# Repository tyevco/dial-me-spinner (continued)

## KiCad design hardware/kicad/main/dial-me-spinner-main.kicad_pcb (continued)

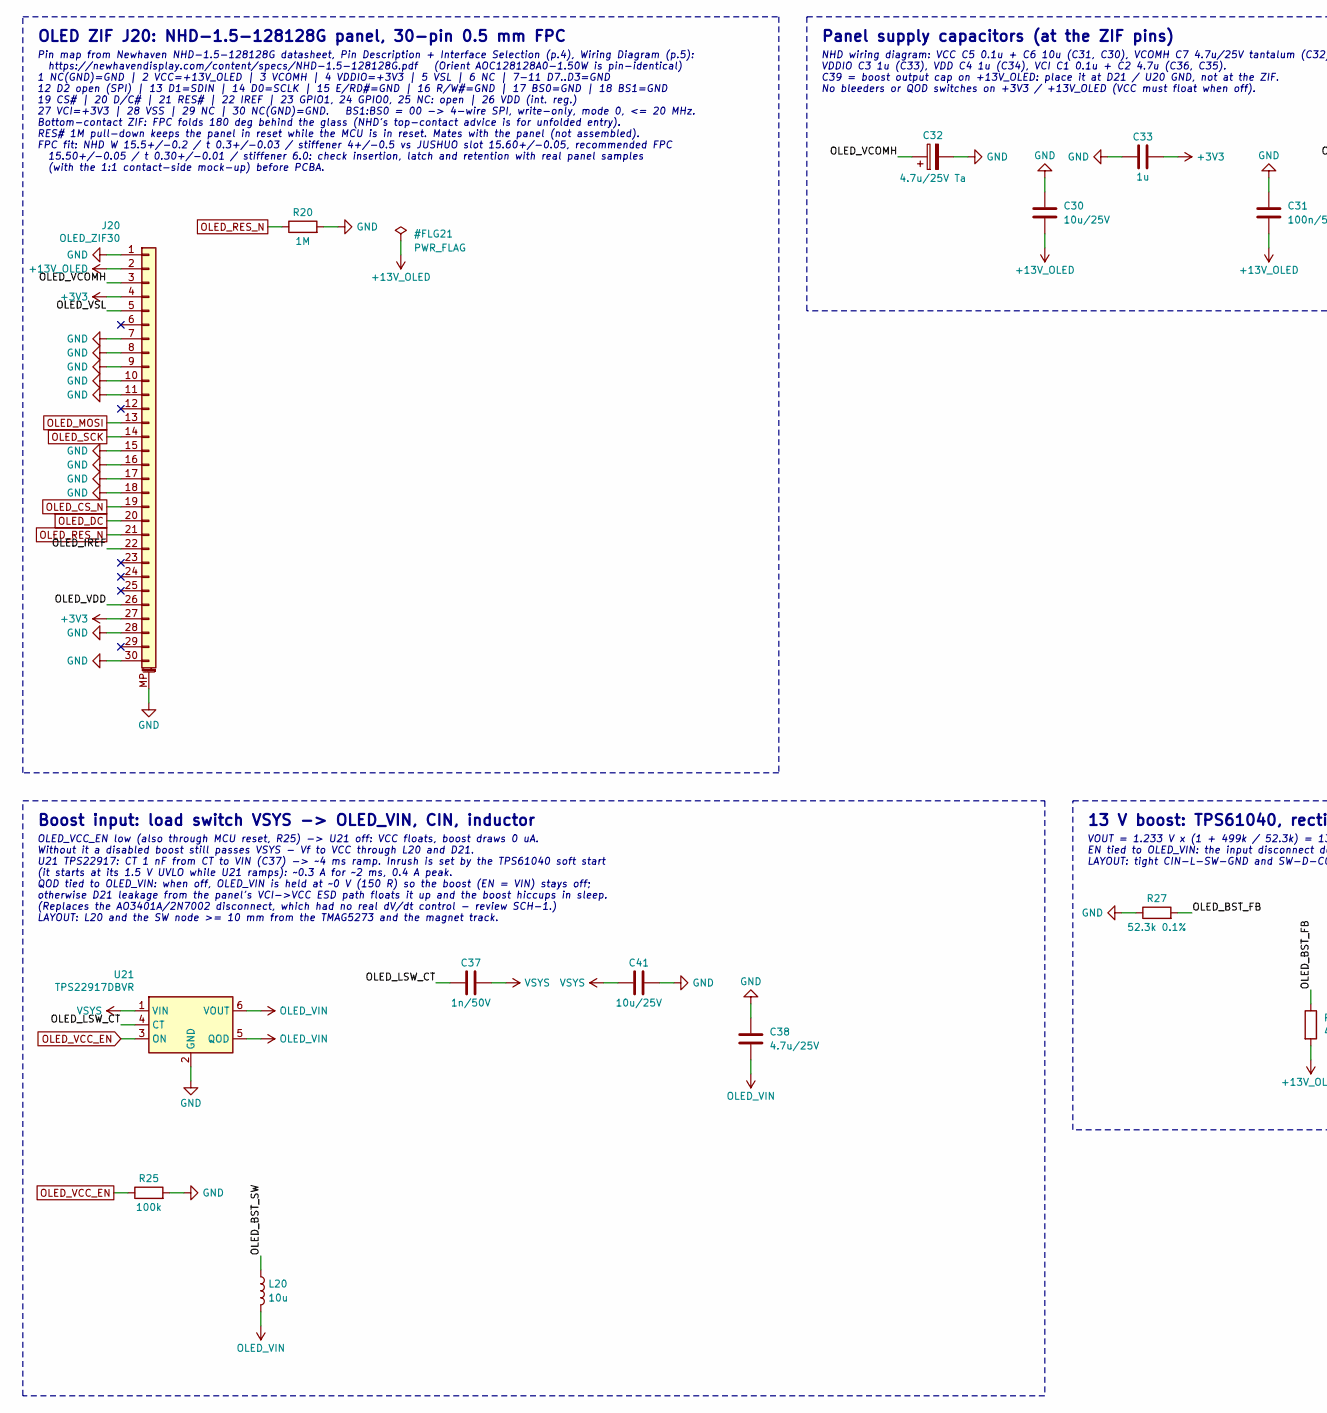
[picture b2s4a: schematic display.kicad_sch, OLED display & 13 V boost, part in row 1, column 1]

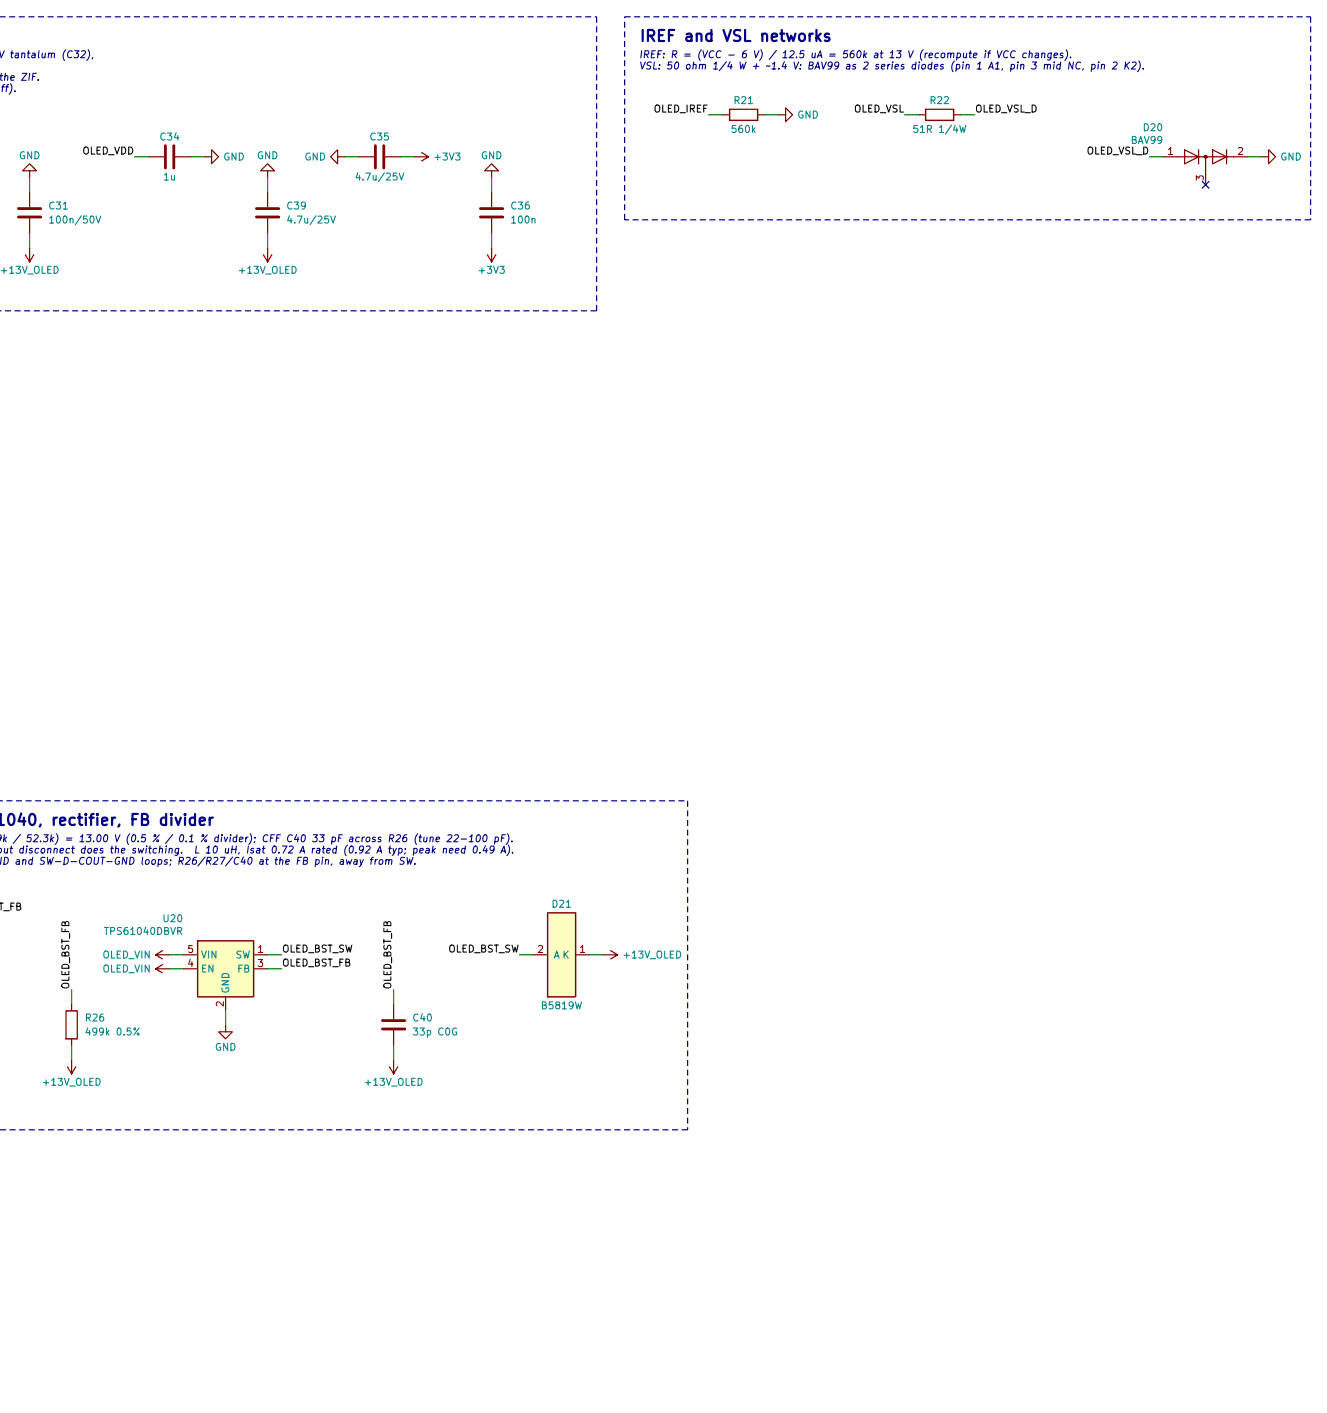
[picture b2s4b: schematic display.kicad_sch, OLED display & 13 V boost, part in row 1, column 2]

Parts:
C30: 10u/25V; C_0805_2012Metric; MPN CL21A106KAYNNNE; LCSC C15850
C31: 100n/50V; C_0402_1005Metric; MPN CL05B104KB54PNC; LCSC C307331
C32: 4.7u/25V Ta; CP_EIA-3216-18_Kemet-A; MPN TAJA475K025RNJ; LCSC C7189
C33, C34: 1u; C_0402_1005Metric; MPN CL05A105KA5NQNC; LCSC C52923
C35, C38, C39: 4.7u/25V; C_0805_2012Metric; MPN CL21A475KAQNNNE; LCSC C1779
C36: 100n; C_0402_1005Metric; MPN CL05B104KO5NNNC; LCSC C1525
C37: 1n/50V; C_0402_1005Metric; MPN 0402B102K500NT; LCSC C1523
C40: 33p C0G; C_0402_1005Metric; MPN 0402CG330J500NT; LCSC C1562
C41: 10u/25V; C_0603_1608Metric; MPN CL10A106MA8NRNC; LCSC C96446
D20: BAV99; SOT-23; MPN BAV99,215; LCSC C2500
D21: B5819W; D_SOD-123; MPN B5819W SL; LCSC C8598
J20: OLED_ZIF30; JUSHUO_AFC01-S30FCA-00_1x30-1MP_P0.50mm_Horizontal; MPN AFC01-S30FCA-00; LCSC C262671
L20: 10u; L_Sunlord_SWPA3015S; MPN SWPA3015S100MT; LCSC C45403
R20: 1M; R_0402_1005Metric; MPN 0402WGF1004TCE; LCSC C26083
R21: 560k; R_0402_1005Metric; MPN 0402WGF5603TCE; LCSC C132339
R22: 51R 1/4W; R_1206_3216Metric; MPN 1206W4F510JT5E; LCSC C18019
R25: 100k; R_0402_1005Metric; MPN 0402WGF1003TCE; LCSC C25741
R26: 499k 0.5%; R_0402_1005Metric; MPN RC0402DR-07499KL; LCSC C4167968
R27: 52.3k 0.1%; R_0402_1005Metric; MPN RT0402BRD0752K3L; LCSC C852832
U20: TPS61040DBVR; SOT-23-5; MPN TPS61040DBVR; LCSC C7722
U21: TPS22917DBVR; SOT-23-6; MPN TPS22917DBVR; LCSC C2681320

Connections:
+3V3: C33.2, C35.2, C36.2, J20.4, J20.27; also elsewhere on the board
+13V_OLED: C30.2, C31.2, C39.2, C40.2, D21.1 (K), J20.2, R26.2
/OLED display & 13 V boost/OLED_BST_FB: C40.1, R26.1, R27.2, U20.3 (FB)
/OLED display & 13 V boost/OLED_BST_SW: D21.2 (A), L20.1, U20.1 (SW)
/OLED display & 13 V boost/OLED_IREF: J20.22, R21.1
/OLED display & 13 V boost/OLED_LSW_CT: C37.1, U21.4 (CT)
/OLED display & 13 V boost/OLED_VCOMH: C32.1, J20.3
/OLED display & 13 V boost/OLED_VDD: C34.1, J20.26
/OLED display & 13 V boost/OLED_VSL: J20.5, R22.1
/OLED display & 13 V boost/OLED_VSL_D: D20.1 (K), R22.2
GND: C30.1, C31.1, C32.2, C33.1, C34.2, C35.1, C36.1, C38.1, C39.1, C41.2, D20.2 (A), J20.1, J20.7, J20.8, J20.9, J20.10, J20.11, J20.15, J20.16, J20.17, J20.18, J20.28, J20.30, J20.MP (MountPin), R20.2, R21.2, R25.2, R27.1, U20.2 (GND), U21.2 (GND); also elsewhere on the board
OLED_CS_N: J20.19; also elsewhere on the board
OLED_DC: J20.20; also elsewhere on the board
OLED_MOSI: J20.13; also elsewhere on the board
OLED_RES_N: J20.21, R20.1; also elsewhere on the board
OLED_SCK: J20.14; also elsewhere on the board
OLED_VCC_EN: R25.1, U21.3 (ON); also elsewhere on the board
OLED_VIN: C38.2, L20.2, U20.4 (EN), U20.5 (VIN), U21.5 (QOD), U21.6 (VOUT)
VSYS: C37.2, C41.1, U21.1 (VIN); also elsewhere on the board

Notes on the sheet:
OLED ZIF J20: NHD-1.5-128128G panel, 30-pin 0.5 mm FPC
Pin map from Newhaven NHD-1.5-128128G datasheet, Pin Description + Interface Selection (p.4), Wiring Diagram (p.5): https://newhavendisplay.com/content/specs/NHD-1.5-128128G.pdf (Orient AOC128128A0-1.50W is pin-identical) 1 NC(GND)=GND | 2 VCC=+13V_OLED | 3 VCOMH | 4 VDDIO=+3V3 | 5 VSL | 6 NC | 7-1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
Panel supply capacitors (at the ZIF pins)
NHD wiring diagram: VCC C5 0.1u + C6 10u (C31, C30), VCOMH C7 4.7u/25V tantalum (C32), VDDIO C3 1u (C33), VDD C4 1u (C34), VCI C1 0.1u + C2 4.7u (C36, C35). C39 = boost output cap on +13V_OLED: place it at D21 / U20 GND, not at the ZIF. No bleeders or QOD switches on +3V3 / +13V_OLED (VCC must floa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
IREF and VSL networks
IREF: R = (VCC - 6 V) / 12.5 uA = 560k at 13 V (recompute if VCC changes). VSL: 50 ohm 1/4 W + ~1.4 V: BAV99 as 2 series diodes (pin 1 A1, pin 3 mid NC, pin 2 K2).
Boost input: load switch VSYS -> OLED_VIN, CIN, inductor
OLED_VCC_EN low (also through MCU reset, R25) -> U21 off: VCC floats, boost draws 0 uA. Without it a disabled boost still passes VSYS - Vf to VCC through L20 and D21. U21 TPS22917: CT 1 nF from CT to VIN (C37) -> ~4 ms ramp. Inrush is set by the TPS61040 soft start (it starts at its 1.5 V UVLO whil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
13 V boost: TPS61040, rectifier, FB divider
VOUT = 1.233 V x (1 + 499k / 52.3k) = 13.00 V (0.5 % / 0.1 % divider); CFF C40 33 pF across R26 (tune 22-100 pF). EN tied to OLED_VIN: the input disconnect does the switching. L 10 uH, Isat 0.72 A rated (0.92 A typ; peak need 0.49 A). LAYOUT: tight CIN-L-SW-GND and SW-D-COUT-GND loops; R26/R27/C40 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

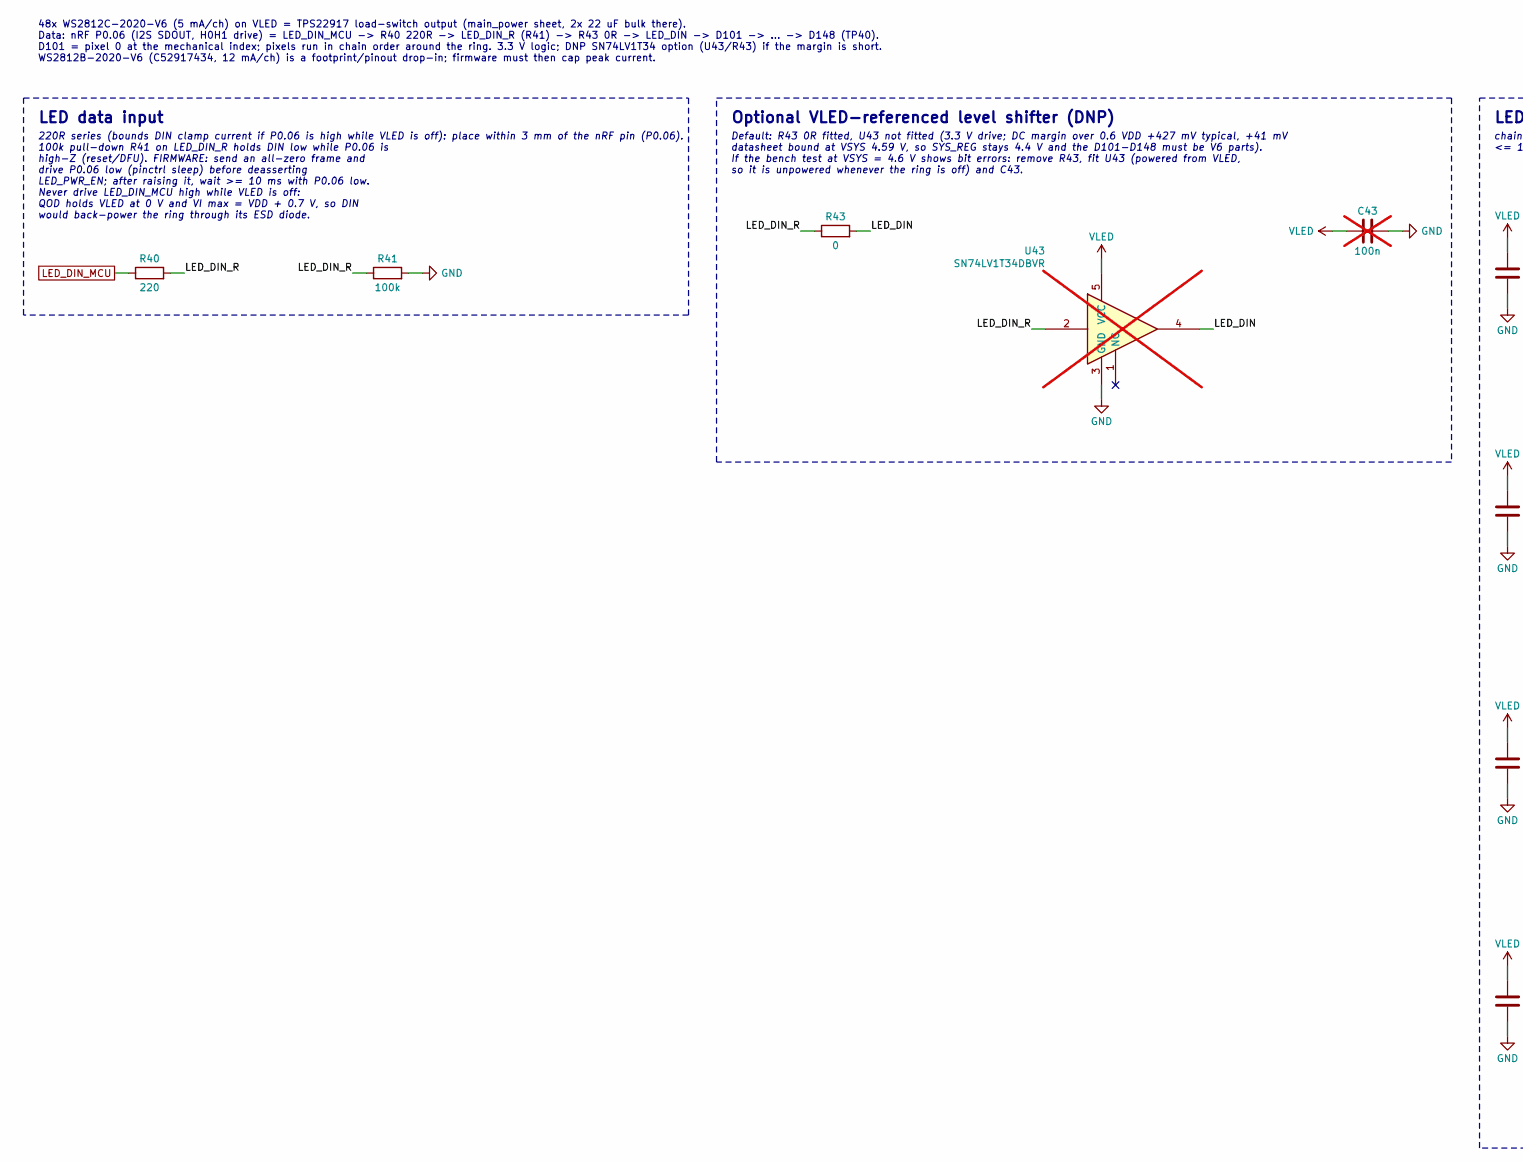
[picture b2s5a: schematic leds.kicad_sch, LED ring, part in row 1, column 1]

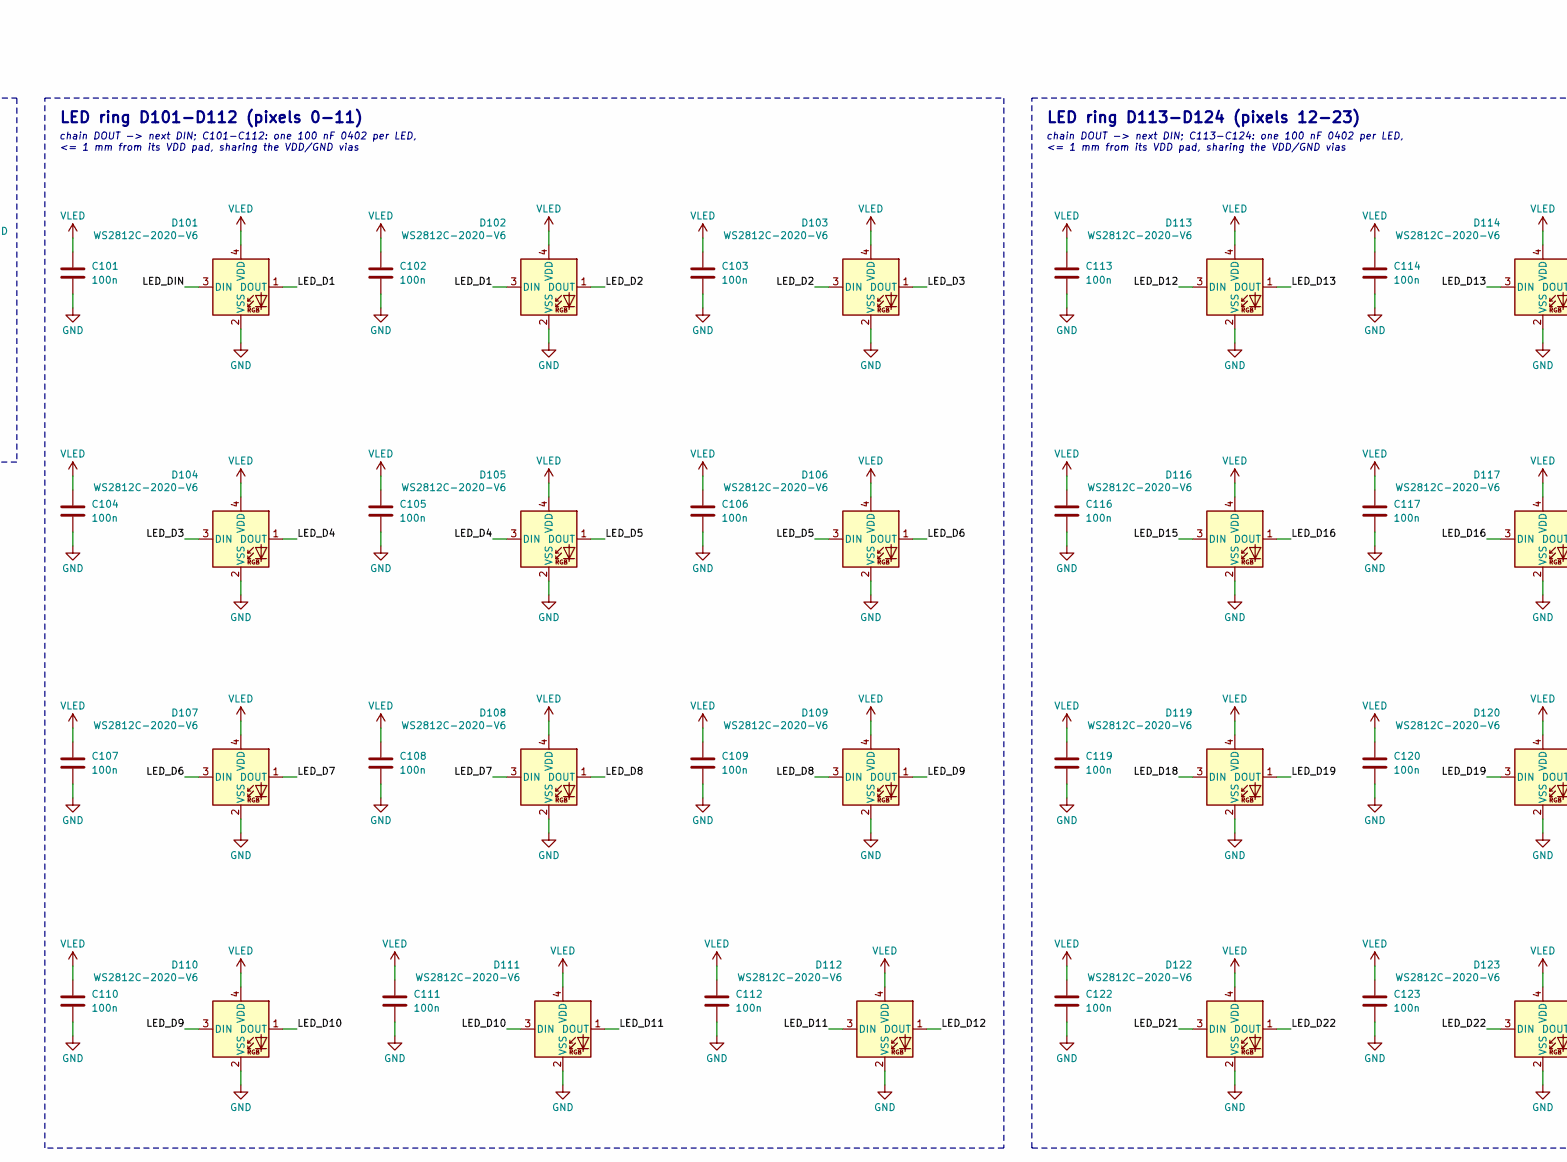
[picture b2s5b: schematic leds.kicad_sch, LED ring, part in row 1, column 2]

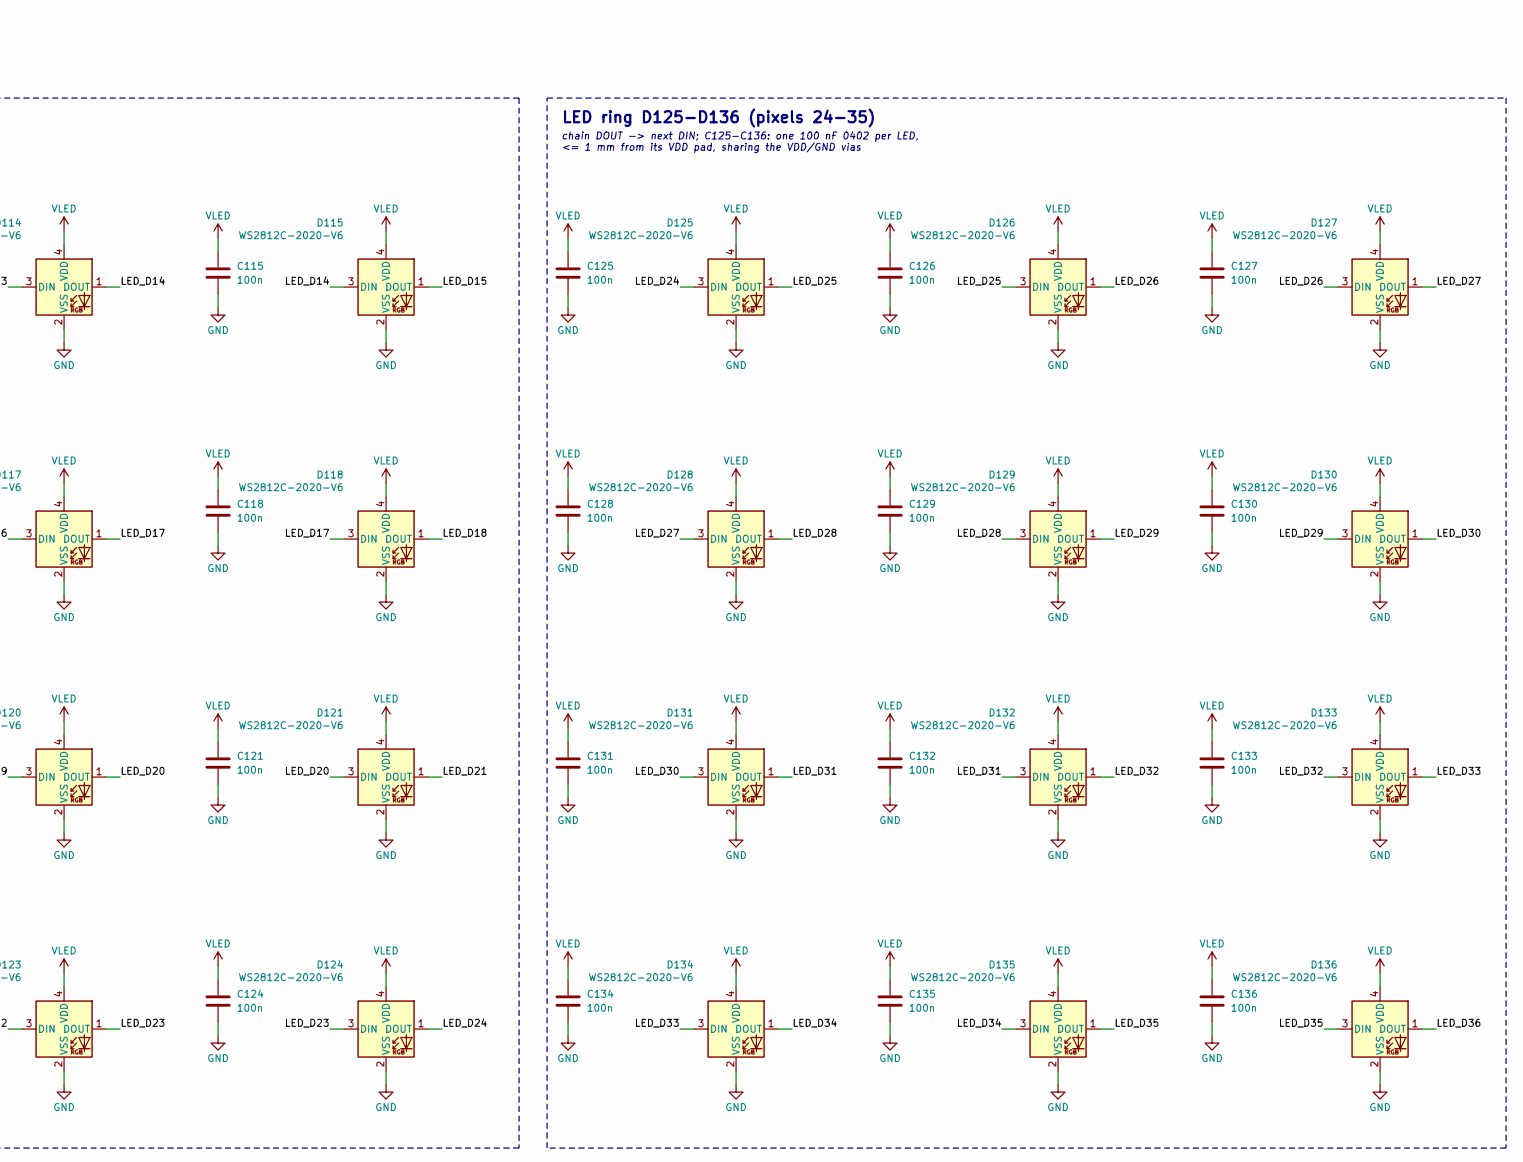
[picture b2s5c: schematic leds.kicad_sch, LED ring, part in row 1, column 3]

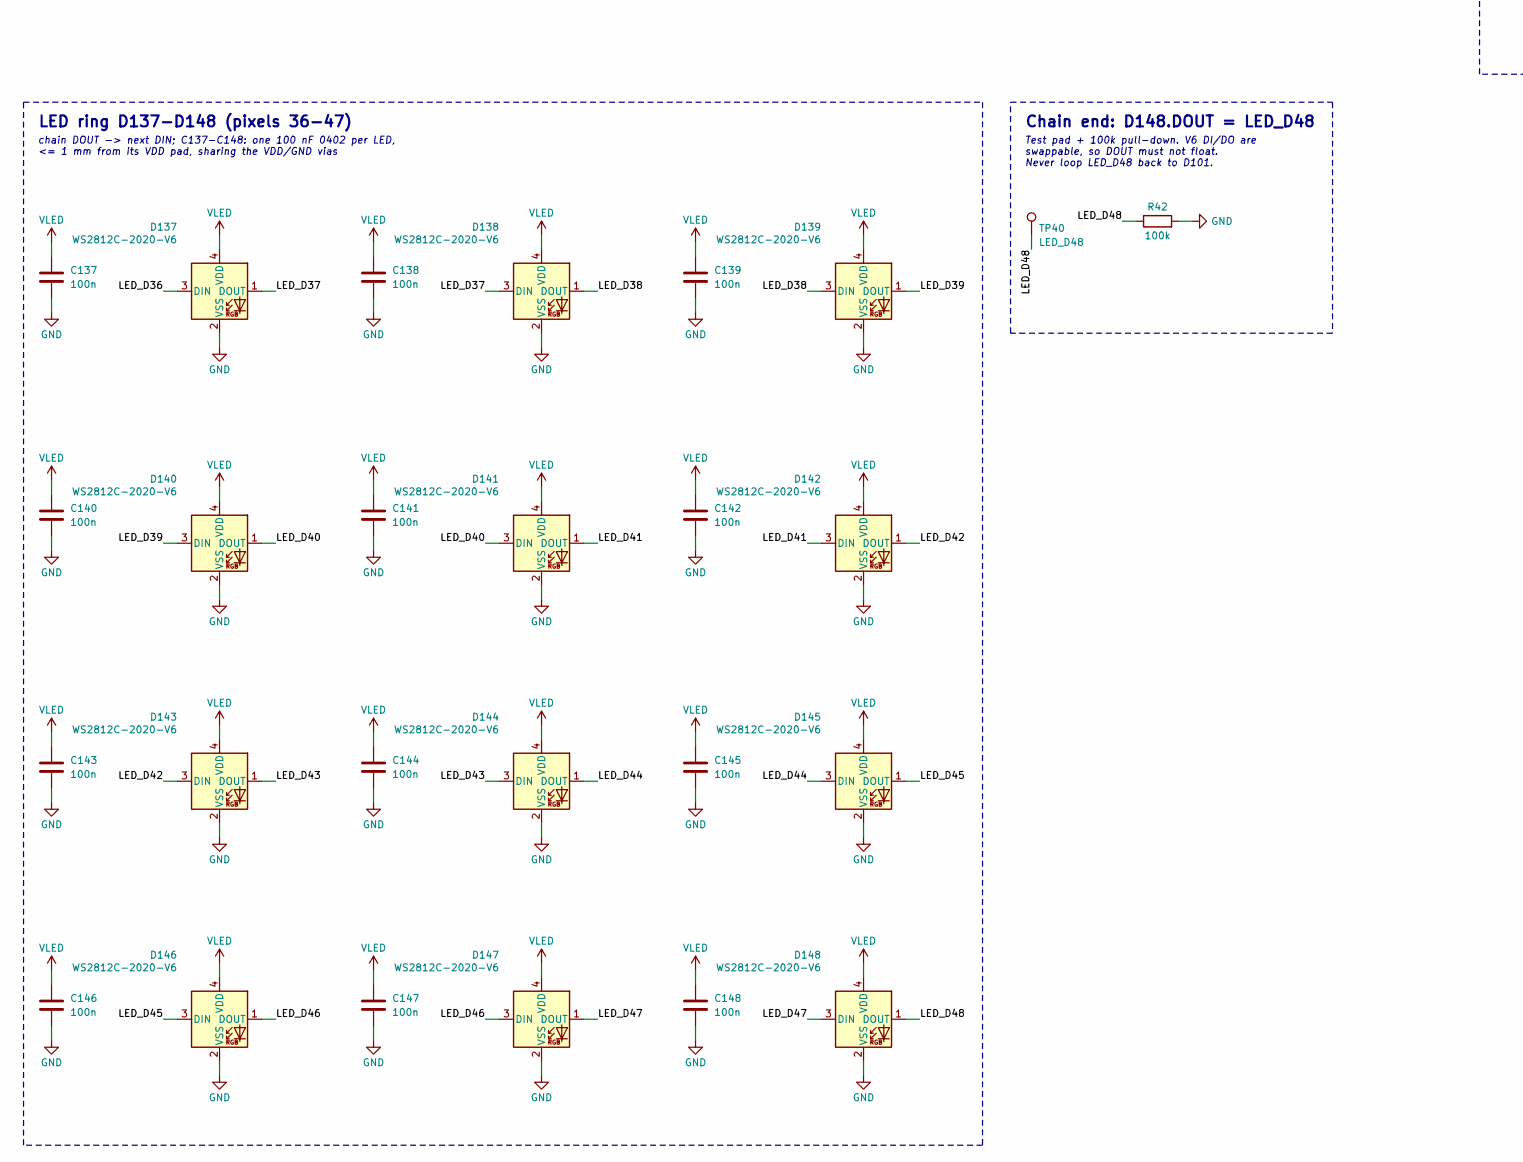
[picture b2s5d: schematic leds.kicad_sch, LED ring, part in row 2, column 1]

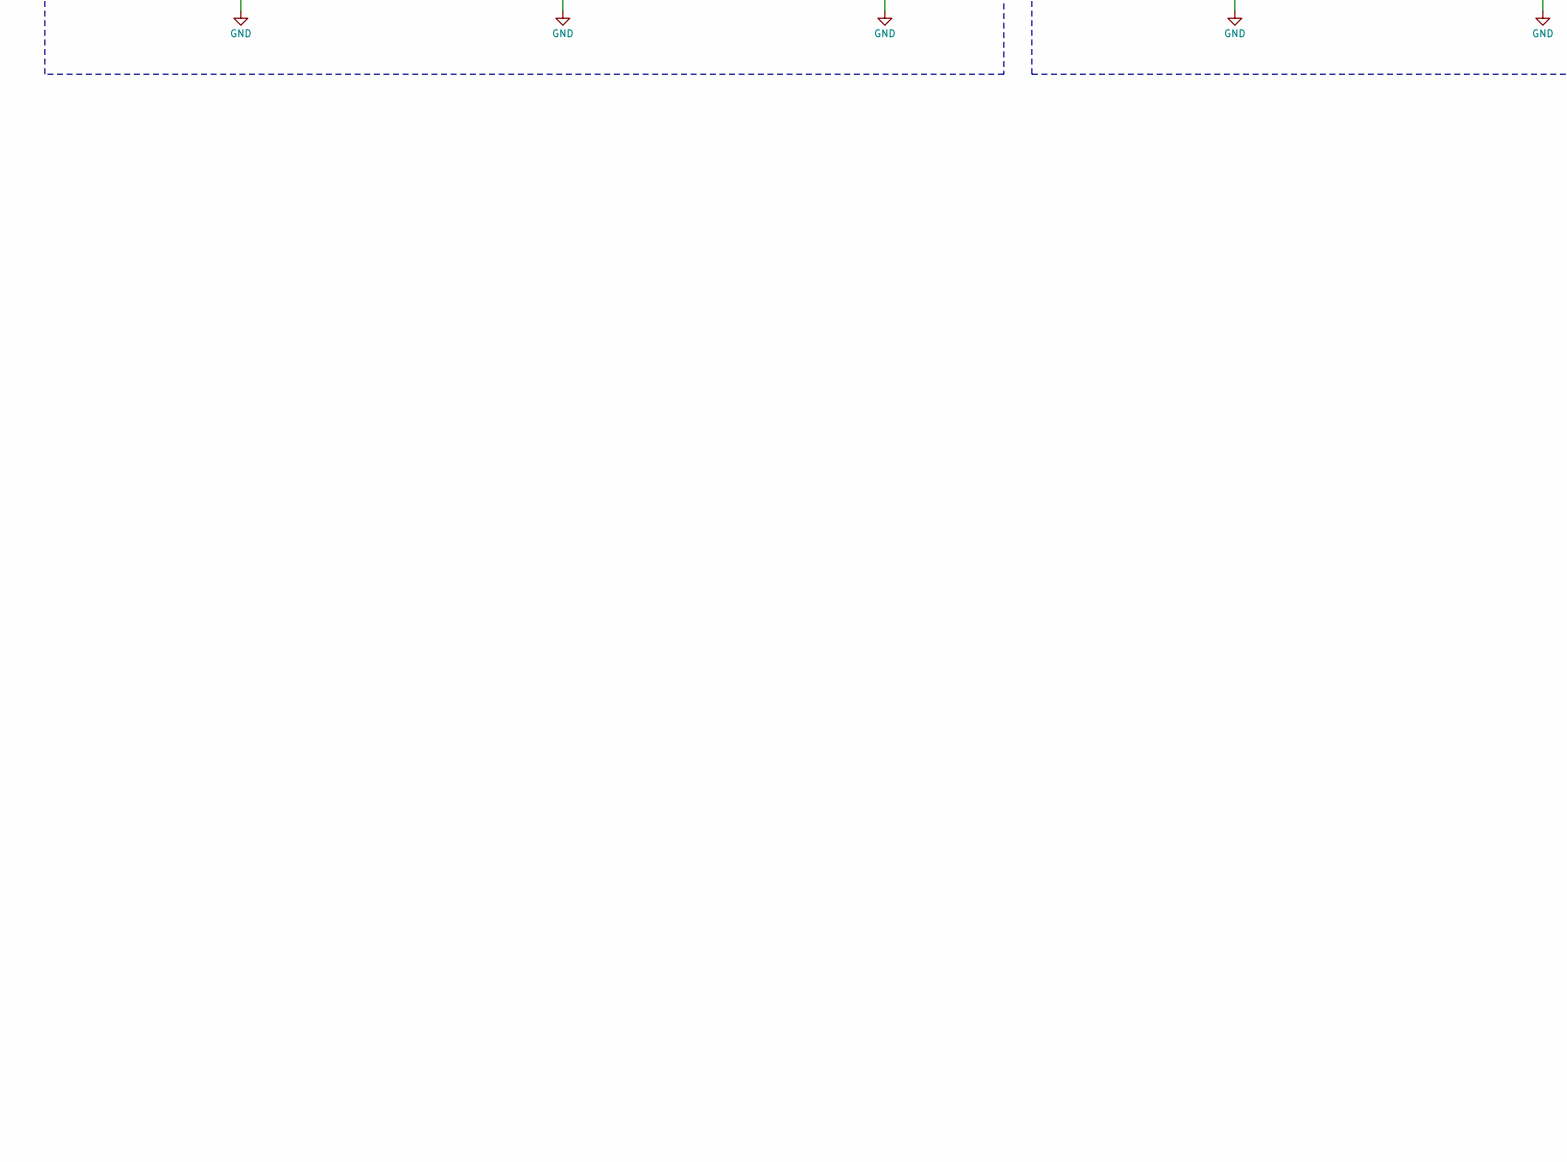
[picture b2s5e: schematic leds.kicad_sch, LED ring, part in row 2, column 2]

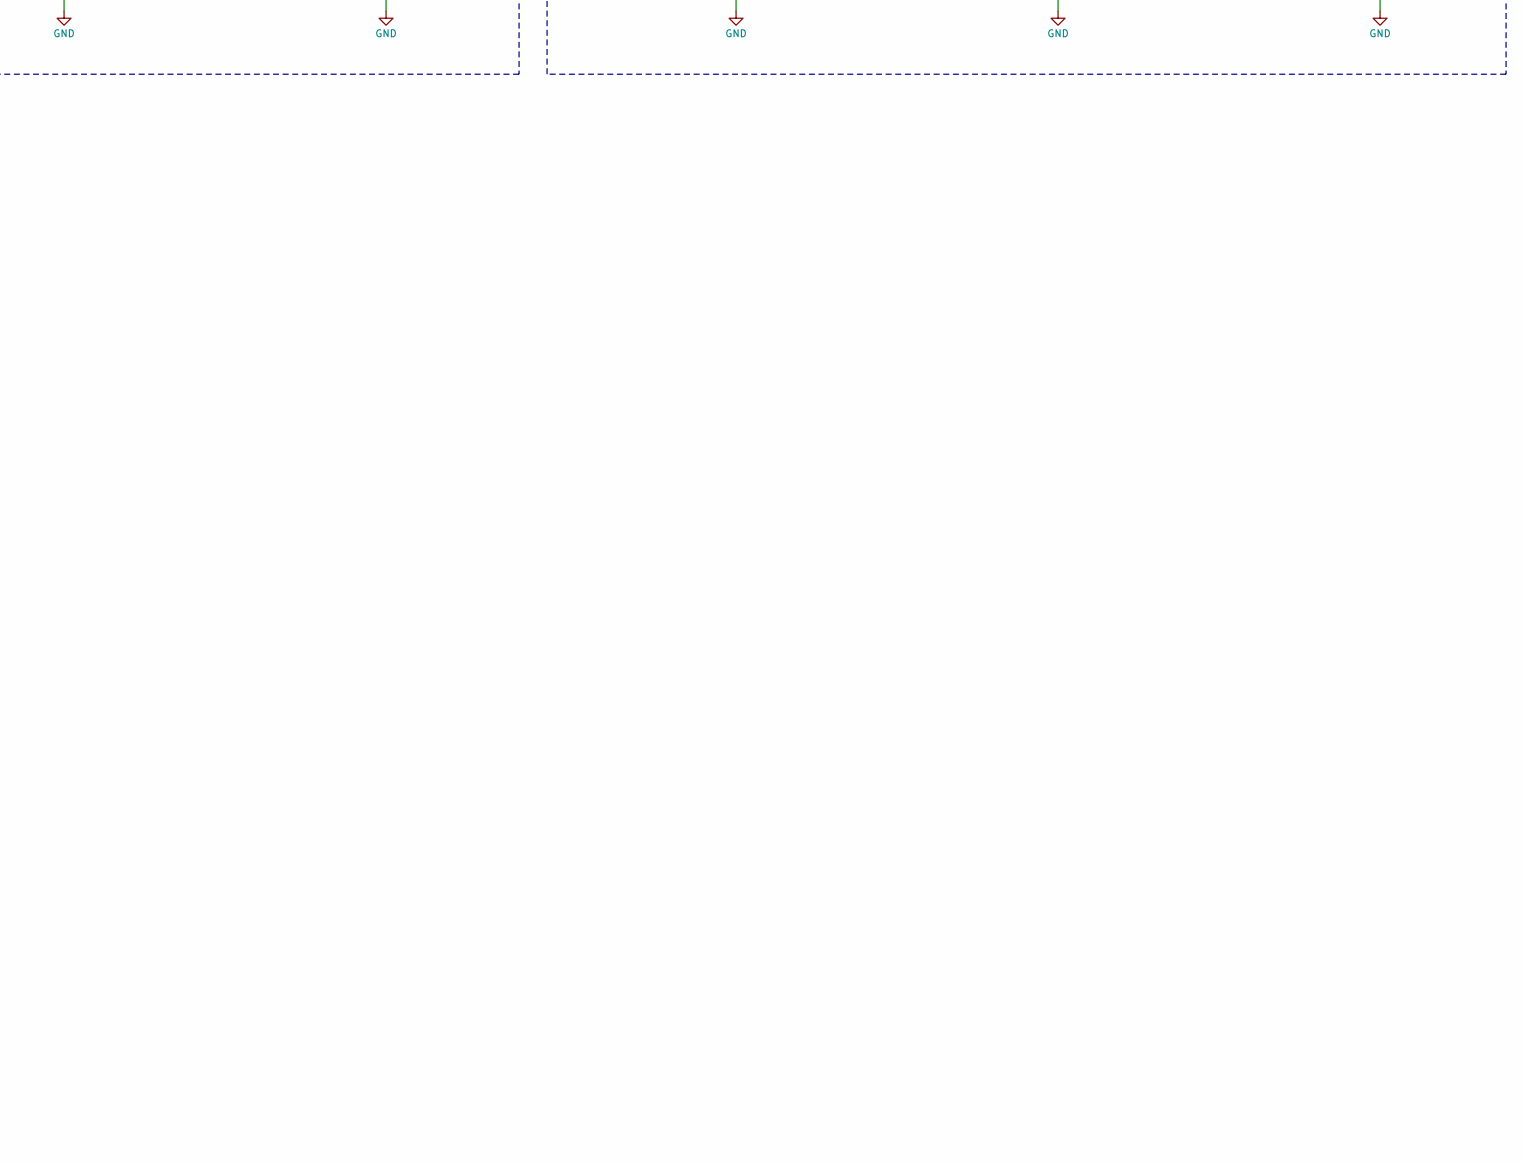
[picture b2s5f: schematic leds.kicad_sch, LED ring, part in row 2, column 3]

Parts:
C43: 100n; C_0402_1005Metric; MPN CL05B104KO5NNNC; LCSC C1525; not fitted
C101, C102, C103, C104, C105, C106, C107, C108, C109, C110, C111, C112, C113, C114, C115, C116, C117, C118, C119, C120, C121, C122, C123, C124, C125, C126, C127, C128, C129, C130, C131, C132, C133, C134, C135, C136, C137, C138, C139, C140, C141, C142, C143, C144, C145, C146, C147, C148: 100n; C_0402_1005Metric; MPN CL05B104KO5NNNC; LCSC C1525
D101, D102, D103, D104, D105, D106, D107, D108, D109, D110, D111, D112, D113, D114, D115, D116, D117, D118, D119, D120, D121, D122, D123, D124, D125, D126, D127, D128, D129, D130, D131, D132, D133, D134, D135, D136, D137, D138, D139, D140, D141, D142, D143, D144, D145, D146, D147, D148: WS2812C-2020-V6; LED_WS2812B-2020_PLCC4_2.0x2.0mm; MPN WS2812C-2020-V6; LCSC C55109522
R40: 220; R_0402_1005Metric; MPN 0402WGF2200TCE; LCSC C25091
R41, R42: 100k; R_0402_1005Metric; MPN 0402WGF1003TCE; LCSC C25741
R43: 0; R_0402_1005Metric; MPN 0402WGF0000TCE; LCSC C17168
TP40: LED_D48; TestPoint_Pad_D1.0mm
U43: SN74LV1T34DBVR; SOT-23-5; MPN SN74LV1T34DBVR; LCSC C100024; not fitted

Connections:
/LED ring/LED_D1: D101.1 (DOUT), D102.3 (DIN)
/LED ring/LED_D2: D102.1 (DOUT), D103.3 (DIN)
/LED ring/LED_D3: D103.1 (DOUT), D104.3 (DIN)
/LED ring/LED_D4: D104.1 (DOUT), D105.3 (DIN)
/LED ring/LED_D5: D105.1 (DOUT), D106.3 (DIN)
/LED ring/LED_D6: D106.1 (DOUT), D107.3 (DIN)
/LED ring/LED_D7: D107.1 (DOUT), D108.3 (DIN)
/LED ring/LED_D8: D108.1 (DOUT), D109.3 (DIN)
/LED ring/LED_D9: D109.1 (DOUT), D110.3 (DIN)
/LED ring/LED_D10: D110.1 (DOUT), D111.3 (DIN)
/LED ring/LED_D11: D111.1 (DOUT), D112.3 (DIN)
/LED ring/LED_D12: D112.1 (DOUT), D113.3 (DIN)
/LED ring/LED_D13: D113.1 (DOUT), D114.3 (DIN)
/LED ring/LED_D14: D114.1 (DOUT), D115.3 (DIN)
/LED ring/LED_D15: D115.1 (DOUT), D116.3 (DIN)
/LED ring/LED_D16: D116.1 (DOUT), D117.3 (DIN)
/LED ring/LED_D17: D117.1 (DOUT), D118.3 (DIN)
/LED ring/LED_D18: D118.1 (DOUT), D119.3 (DIN)
/LED ring/LED_D19: D119.1 (DOUT), D120.3 (DIN)
/LED ring/LED_D20: D120.1 (DOUT), D121.3 (DIN)
/LED ring/LED_D21: D121.1 (DOUT), D122.3 (DIN)
/LED ring/LED_D22: D122.1 (DOUT), D123.3 (DIN)
/LED ring/LED_D23: D123.1 (DOUT), D124.3 (DIN)
/LED ring/LED_D24: D124.1 (DOUT), D125.3 (DIN)
/LED ring/LED_D25: D125.1 (DOUT), D126.3 (DIN)
/LED ring/LED_D26: D126.1 (DOUT), D127.3 (DIN)
/LED ring/LED_D27: D127.1 (DOUT), D128.3 (DIN)
/LED ring/LED_D28: D128.1 (DOUT), D129.3 (DIN)
/LED ring/LED_D29: D129.1 (DOUT), D130.3 (DIN)
/LED ring/LED_D30: D130.1 (DOUT), D131.3 (DIN)
/LED ring/LED_D31: D131.1 (DOUT), D132.3 (DIN)
/LED ring/LED_D32: D132.1 (DOUT), D133.3 (DIN)
/LED ring/LED_D33: D133.1 (DOUT), D134.3 (DIN)
/LED ring/LED_D34: D134.1 (DOUT), D135.3 (DIN)
/LED ring/LED_D35: D135.1 (DOUT), D136.3 (DIN)
/LED ring/LED_D36: D136.1 (DOUT), D137.3 (DIN)
/LED ring/LED_D37: D137.1 (DOUT), D138.3 (DIN)
/LED ring/LED_D38: D138.1 (DOUT), D139.3 (DIN)
/LED ring/LED_D39: D139.1 (DOUT), D140.3 (DIN)
/LED ring/LED_D40: D140.1 (DOUT), D141.3 (DIN)
/LED ring/LED_D41: D141.1 (DOUT), D142.3 (DIN)
/LED ring/LED_D42: D142.1 (DOUT), D143.3 (DIN)
/LED ring/LED_D43: D143.1 (DOUT), D144.3 (DIN)
/LED ring/LED_D44: D144.1 (DOUT), D145.3 (DIN)
/LED ring/LED_D45: D145.1 (DOUT), D146.3 (DIN)
/LED ring/LED_D46: D146.1 (DOUT), D147.3 (DIN)
/LED ring/LED_D47: D147.1 (DOUT), D148.3 (DIN)
/LED ring/LED_D48: D148.1 (DOUT), R42.1, TP40.1
/LED ring/LED_DIN: D101.3 (DIN), R43.2, U43.4
/LED ring/LED_DIN_R: R40.2, R41.1, R43.1, U43.2
GND: C43.2, C101.2, C102.2, C103.2, C104.2, C105.2, C106.2, C107.2, C108.2, C109.2, C110.2, C111.2, C112.2, C113.2, C114.2, C115.2, C116.2, C117.2, C118.2, C119.2, C120.2, C121.2, C122.2, C123.2, C124.2, C125.2, C126.2, C127.2, C128.2, C129.2, C130.2, C131.2, C132.2, C133.2, C134.2, C135.2, C136.2, C137.2, C138.2, C139.2, C140.2, C141.2, C142.2, C143.2, C144.2, C145.2, C146.2, C147.2, C148.2, D101.2 (VSS), D102.2 (VSS), D103.2 (VSS), D104.2 (VSS), D105.2 (VSS), D106.2 (VSS), D107.2 (VSS), D108.2 (VSS), D109.2 (VSS), D110.2 (VSS), D111.2 (VSS), D112.2 (VSS), D113.2 (VSS), D114.2 (VSS), D115.2 (VSS), D116.2 (VSS), D117.2 (VSS), D118.2 (VSS), D119.2 (VSS), D120.2 (VSS), D121.2 (VSS), D122.2 (VSS), D123.2 (VSS), D124.2 (VSS), D125.2 (VSS), D126.2 (VSS), D127.2 (VSS), D128.2 (VSS), D129.2 (VSS), D130.2 (VSS), D131.2 (VSS), D132.2 (VSS), D133.2 (VSS), D134.2 (VSS), D135.2 (VSS), D136.2 (VSS), D137.2 (VSS), D138.2 (VSS), D139.2 (VSS), D140.2 (VSS), D141.2 (VSS), D142.2 (VSS), D143.2 (VSS), D144.2 (VSS), D145.2 (VSS), D146.2 (VSS), D147.2 (VSS), D148.2 (VSS), R41.2, R42.2, U43.3 (GND); also elsewhere on the board
LED_DIN_MCU: R40.1; also elsewhere on the board
VLED: C43.1, C101.1, C102.1, C103.1, C104.1, C105.1, C106.1, C107.1, C108.1, C109.1, C110.1, C111.1, C112.1, C113.1, C114.1, C115.1, C116.1, C117.1, C118.1, C119.1, C120.1, C121.1, C122.1, C123.1, C124.1, C125.1, C126.1, C127.1, C128.1, C129.1, C130.1, C131.1, C132.1, C133.1, C134.1, C135.1, C136.1, C137.1, C138.1, C139.1, C140.1, C141.1, C142.1, C143.1, C144.1, C145.1, C146.1, C147.1, C148.1, D101.4 (VDD), D102.4 (VDD), D103.4 (VDD), D104.4 (VDD), D105.4 (VDD), D106.4 (VDD), D107.4 (VDD), D108.4 (VDD), D109.4 (VDD), D110.4 (VDD), D111.4 (VDD), D112.4 (VDD), D113.4 (VDD), D114.4 (VDD), D115.4 (VDD), D116.4 (VDD), D117.4 (VDD), D118.4 (VDD), D119.4 (VDD), D120.4 (VDD), D121.4 (VDD), D122.4 (VDD), D123.4 (VDD), D124.4 (VDD), D125.4 (VDD), D126.4 (VDD), D127.4 (VDD), D128.4 (VDD), D129.4 (VDD), D130.4 (VDD), D131.4 (VDD), D132.4 (VDD), D133.4 (VDD), D134.4 (VDD), D135.4 (VDD), D136.4 (VDD), D137.4 (VDD), D138.4 (VDD), D139.4 (VDD), D140.4 (VDD), D141.4 (VDD), D142.4 (VDD), D143.4 (VDD), D144.4 (VDD), D145.4 (VDD), D146.4 (VDD), D147.4 (VDD), D148.4 (VDD), U43.5 (VCC); also elsewhere on the board

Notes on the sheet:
48x WS2812C-2020-V6 (5 mA/ch) on VLED = TPS22917 load-switch output (main_power sheet, 2x 22 uF bulk there). Data: nRF P0.06 (I2S SDOUT, H0H1 drive) = LED_DIN_MCU -> R40 220R -> LED_DIN_R (R41) -> R43 0R -> LED_DIN -> D101 -> ... -> D148 (TP40). D101 = pixel 0 at the mechanical index; pixels run in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
LED data input
220R series (bounds DIN clamp current if P0.06 is high while VLED is off): place within 3 mm of the nRF pin (P0.06). 100k pull-down R41 on LED_DIN_R holds DIN low while P0.06 is high-Z (reset/DFU). FIRMWARE: send an all-zero frame and drive P0.06 low (pinctrl sleep) before deasserting LED_PWR_EN; a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
Optional VLED-referenced level shifter (DNP)
Default: R43 0R fitted, U43 not fitted (3.3 V drive; DC margin over 0.6 VDD +427 mV typical, +41 mV datasheet bound at VSYS 4.59 V, so SYS_REG stays 4.4 V and the D101-D148 must be V6 parts). If the bench test at VSYS = 4.6 V shows bit errors: remove R43, fit U43 (powered from VLED, so it is unpowe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
LED ring D101-D112 (pixels 0-11)
chain DOUT -> next DIN; C101-C112: one 100 nF 0402 per LED, <= 1 mm from its VDD pad, sharing the VDD/GND vias
LED ring D113-D124 (pixels 12-23)
chain DOUT -> next DIN; C113-C124: one 100 nF 0402 per LED, <= 1 mm from its VDD pad, sharing the VDD/GND vias
LED ring D125-D136 (pixels 24-35)
chain DOUT -> next DIN; C125-C136: one 100 nF 0402 per LED, <= 1 mm from its VDD pad, sharing the VDD/GND vias
LED ring D137-D148 (pixels 36-47)
chain DOUT -> next DIN; C137-C148: one 100 nF 0402 per LED, <= 1 mm from its VDD pad, sharing the VDD/GND vias
Chain end: D148.DOUT = LED_D48
Test pad + 100k pull-down. V6 DI/DO are swappable, so DOUT must not float. Never loop LED_D48 back to D101.
